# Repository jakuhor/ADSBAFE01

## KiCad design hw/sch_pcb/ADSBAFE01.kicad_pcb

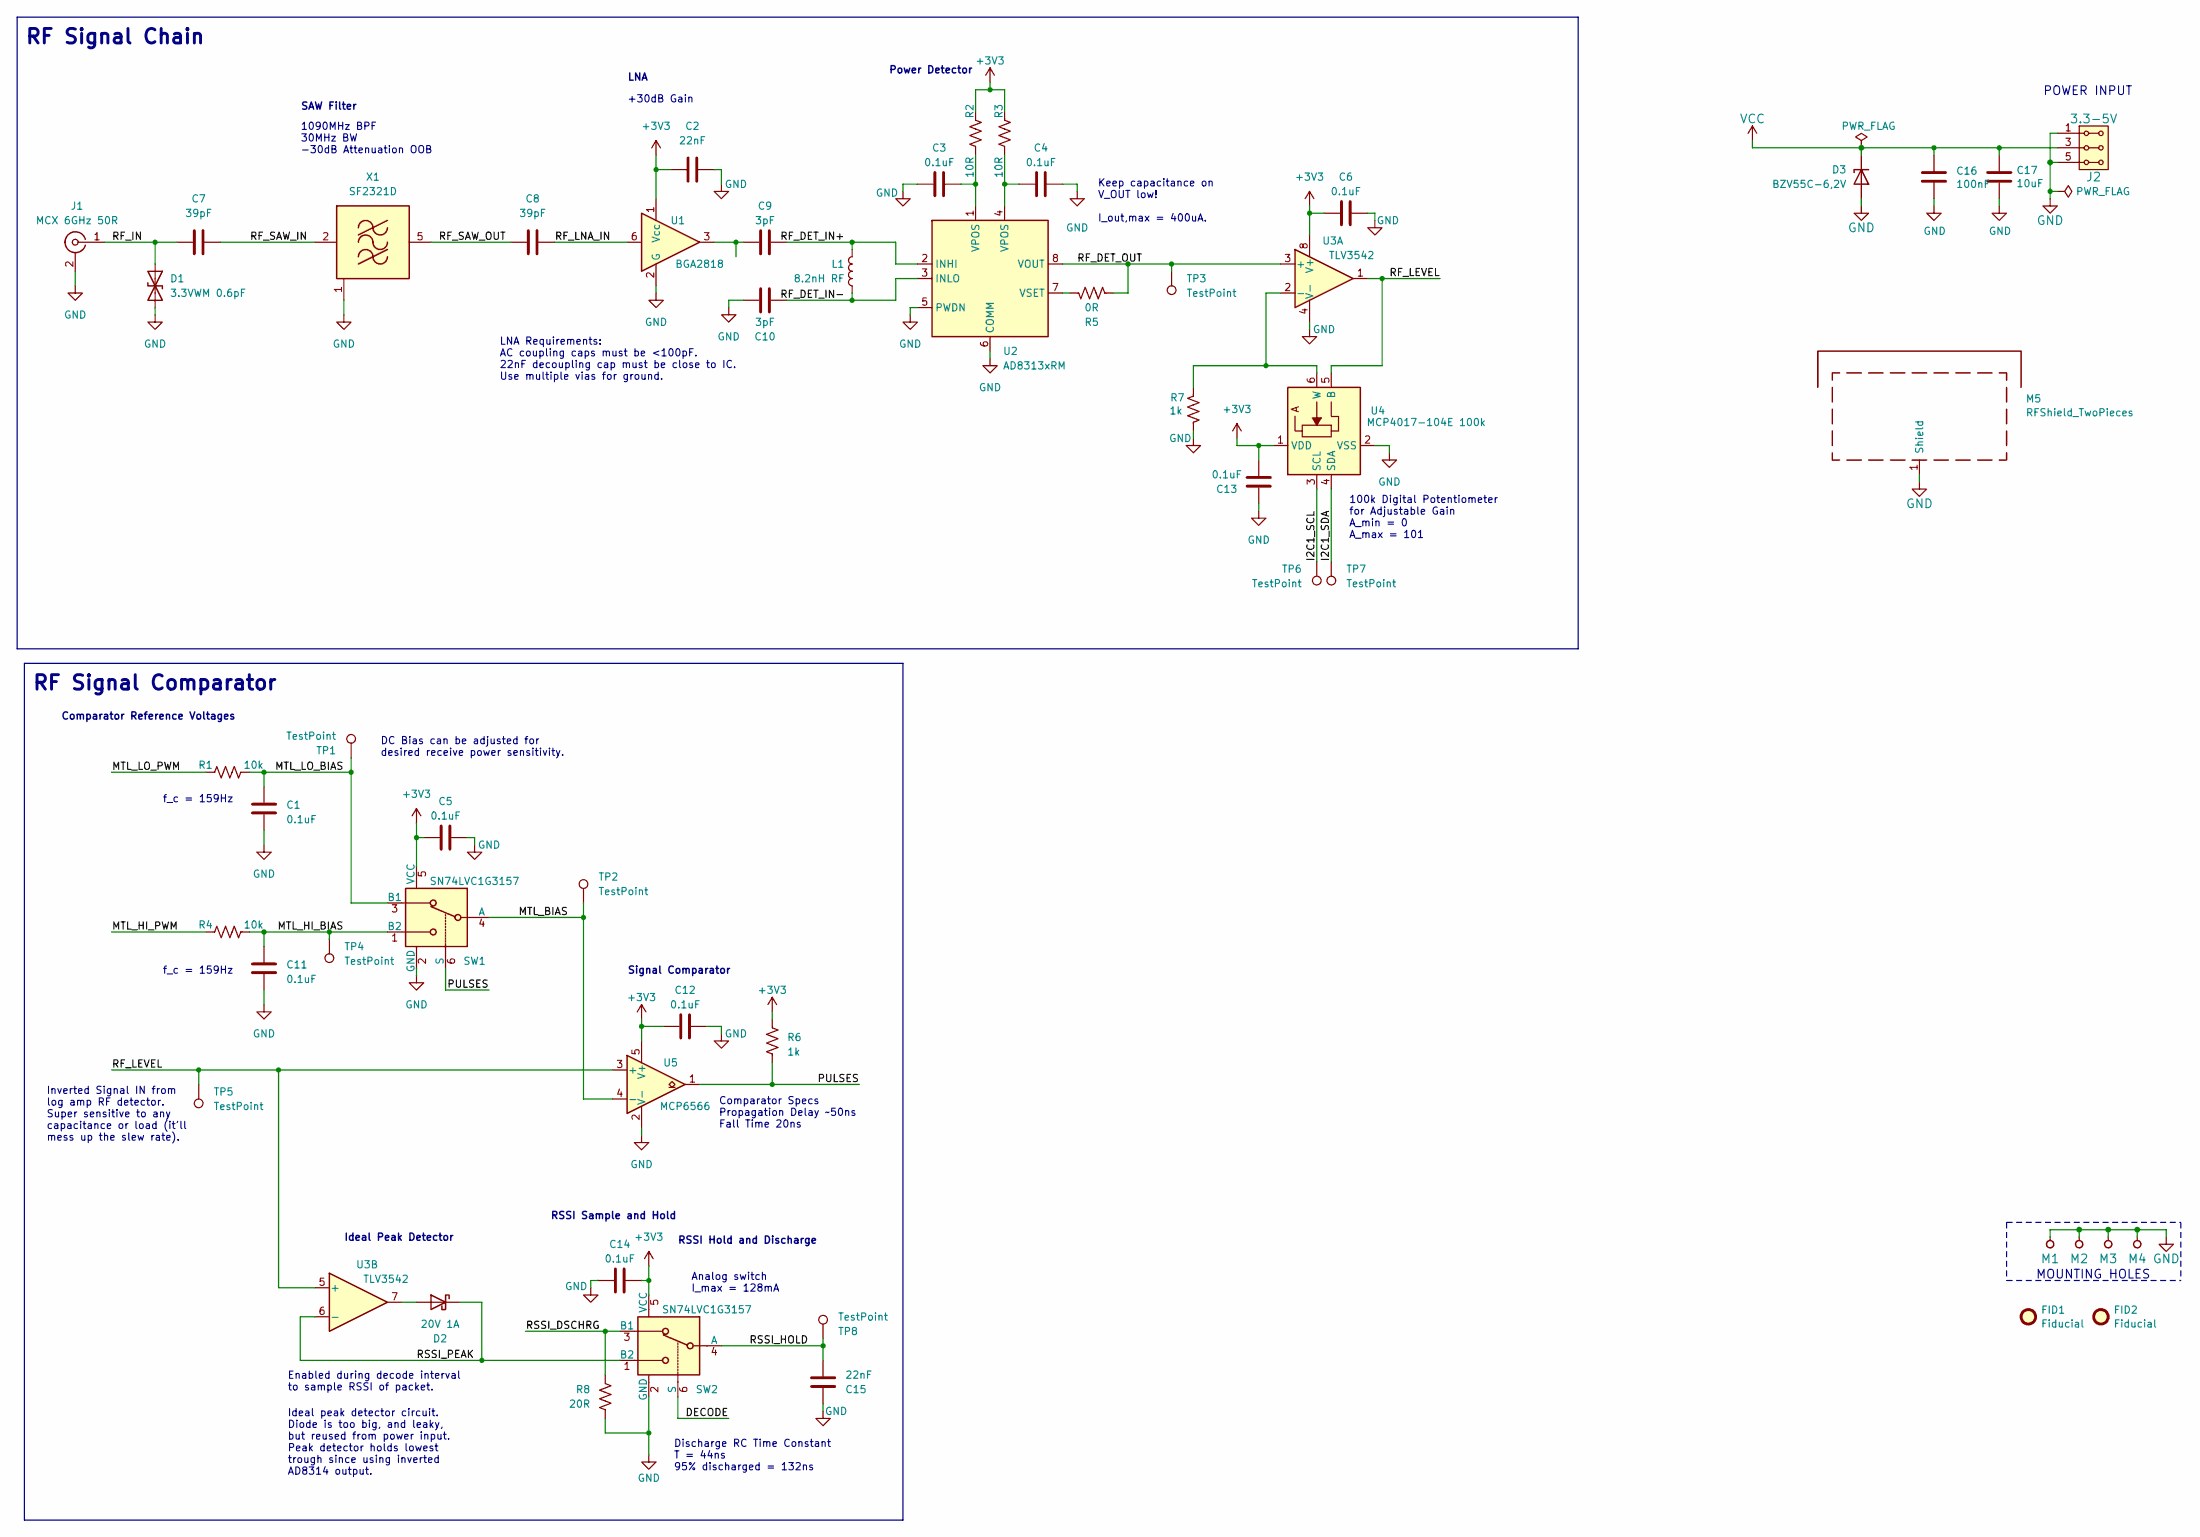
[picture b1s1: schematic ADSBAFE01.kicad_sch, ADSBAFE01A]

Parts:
C1, C3, C4, C5, C6, C11, C12, C13, C14: 0.1uF; C_0402_1005Metric; MPN C60474
C2, C15: 22nF; C_0402_1005Metric; MPN C107026
C7, C8: 39pF; C_0402_1005Metric; MPN C106223
C9, C10: 3pF; C_0402_1005Metric; MPN C1855211
C16: 100nF; C_0805_2012Metric
C17: 10uF; C_0805_2012Metric
D1: 3.3VWM 0.6pF; D_SOD-523; MPN C2912559
D2: 20V 1A; D_SOD-123; MPN C82288
D3: BZV55C-6,2V; D_MiniMELF
FID1, FID2: Fiducial; Fiducial_1mm_Mask2mm
J1: MCX 6GHz 50R; MCX; MPN C88374
J2: 3.3-5V; Straight_2x03
L1: 8.2nH RF; L_0402_1005Metric; MPN C361505
M1, M2, M3, M4: HOLE; MountingHole_3mm
M5: RFShield_TwoPieces; Laird_Technologies_BMI-S-204-F_32.00x32.00mm
R1, R4: 10k; R_0402_1005Metric; MPN C60490
R2, R3: 10R; R_0402_1005Metric; MPN C138066
R5: 0R; R_0402_1005Metric; MPN C60485
R6, R7: 1k; R_0402_1005Metric; MPN C106235
R8: 20R; R_0402_1005Metric; MPN C138031
SW1, SW2: SN74LVC1G3157; SOT-363_SC-70-6; MPN C38663
TP1, TP2, TP3, TP4, TP5, TP6, TP7, TP8: TestPoint; TestPoint_Pad_D1.0mm
U1: BGA2818; SOT-363_SC-70-6; MPN None
U2: AD8313xRM; MSOP-8_3x3mm_P0.65mm; MPN C481897
U3: TLV3542; VSSOP-8_3.0x3.0mm_P0.65mm; MPN C2876465
U4: MCP4017-104E 100k; SOT-363_SC-70-6; MPN C510890
U5: MCP6566; SOT-353_SC-70-5; MPN C623508
X1: SF2321D; Filter_SAW-6_3.8x3.8mm; MPN C3283372

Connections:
+3V3: C2.1, C5.1, C6.1, C12.1, C13.2, C14.2, R2.1, R3.1, R6.1, SW1.5 (VCC), SW2.5 (VCC), U1.1 (Vcc), U3.8 (V+), U4.1 (VDD), U5.5 (V+)
/DECODE: SW2.6 (S)
/I2C1_SCL: TP6.1, U4.3 (SCL)
/I2C1_SDA: TP7.1, U4.4 (SDA)
/MTL_BIAS: SW1.4 (A), TP2.1, U5.4 (-)
/MTL_HI_BIAS: C11.1, R4.1, SW1.1 (B2), TP4.1
/MTL_HI_PWM: R4.2
/MTL_LO_BIAS: C1.1, R1.1, SW1.3 (B1), TP1.1
/MTL_LO_PWM: R1.2
/PULSES: R6.2, SW1.6 (S), U5.1
/RF_DET_IN+: C9.2, L1.1, U2.2 (INHI)
/RF_DET_IN-: C10.2, L1.2, U2.3 (INLO)
/RF_DET_OUT: R5.2, TP3.1, U2.8 (VOUT), U3.3 (+)
/RF_IN: C7.1, D1.1 (A1), J1.1 (In)
/RF_LEVEL: TP5.1, U3.1, U3.5 (+), U4.5 (B), U5.3 (+)
/RF_LNA_IN: C8.2, U1.6
/RF_SAW_IN: C7.2, X1.2 (IN)
/RF_SAW_OUT: C8.1, X1.5 (OUT)
/RSSI_DSCHRG: R8.1, SW2.3 (B1)
/RSSI_HOLD: C15.2, SW2.4 (A), TP8.1
/RSSI_PEAK: D2.1 (K), SW2.1 (B2), U3.6 (-)
GND: C1.2, C2.2, C3.1, C4.2, C5.2, C6.2, C10.1, C11.2, C12.2, C13.1, C14.1, C15.1, C16.2, C17.2, D1.2 (A2), D3.2 (A), J1.2 (Ext), J2.1, J2.2, J2.5, J2.6, M1.1, M2.1, M3.1, M4.1, M5.1 (Shield), R7.2, R8.2, SW1.2 (GND), SW2.2 (GND), U1.2 (G), U1.4 (G), U1.5 (G), U2.5 (PWDN), U2.6 (COMM), U3.4 (V-), U4.2 (VSS), U5.2 (V-), X1.1 (GND), X1.3 (GND), X1.4 (GND), X1.6 (GND)
unnamed: C3.2, R2.2, U2.1 (VPOS)
unnamed: C4.1, R3.2, U2.4 (VPOS)
unnamed: C9.1, U1.3
unnamed: D2.2 (A), U3.7
unnamed: R5.1, U2.7 (VSET)
unnamed: R7.1, U3.2 (-), U4.6 (W)
VCC: C16.1, C17.1, D3.1 (K), J2.3, J2.4

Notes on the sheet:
LNA
Comparator Reference Voltages
1090MHz BPF 30MHz BW -30dB Attenuation OOB
Keep capacitance on V_OUT low! I_out,max = 400uA.
100k Digital Potentiometer for Adjustable Gain A_min = 0 A_max = 101
Ideal Peak Detector
f_c = 159Hz
Analog switch I_max = 128mA
Enabled during decode interval to sample RSSI of packet.
RF Signal Comparator
SAW Filter
MOUNTING HOLES
RF Signal Chain
+30dB Gain
Signal Comparator
f_c = 159Hz
Comparator Specs Propagation Delay ~50ns Fall Time 20ns
RSSI Sample and Hold
DC Bias can be adjusted for desired receive power sensitivity.
LNA Requirements: AC coupling caps must be <100pF. 22nF decoupling cap must be close to IC. Use multiple vias for ground.
RSSI Hold and Discharge
POWER INPUT
Ideal peak detector circuit. Diode is too big, and leaky, but reused from power input. Peak detector holds lowest trough since using inverted AD8314 output.
Power Detector
Discharge RC Time Constant T = 44ns 95% discharged = 132ns
Inverted Signal IN from log amp RF detector. Super sensitive to any capacitance or load (it'll mess up the slew rate).

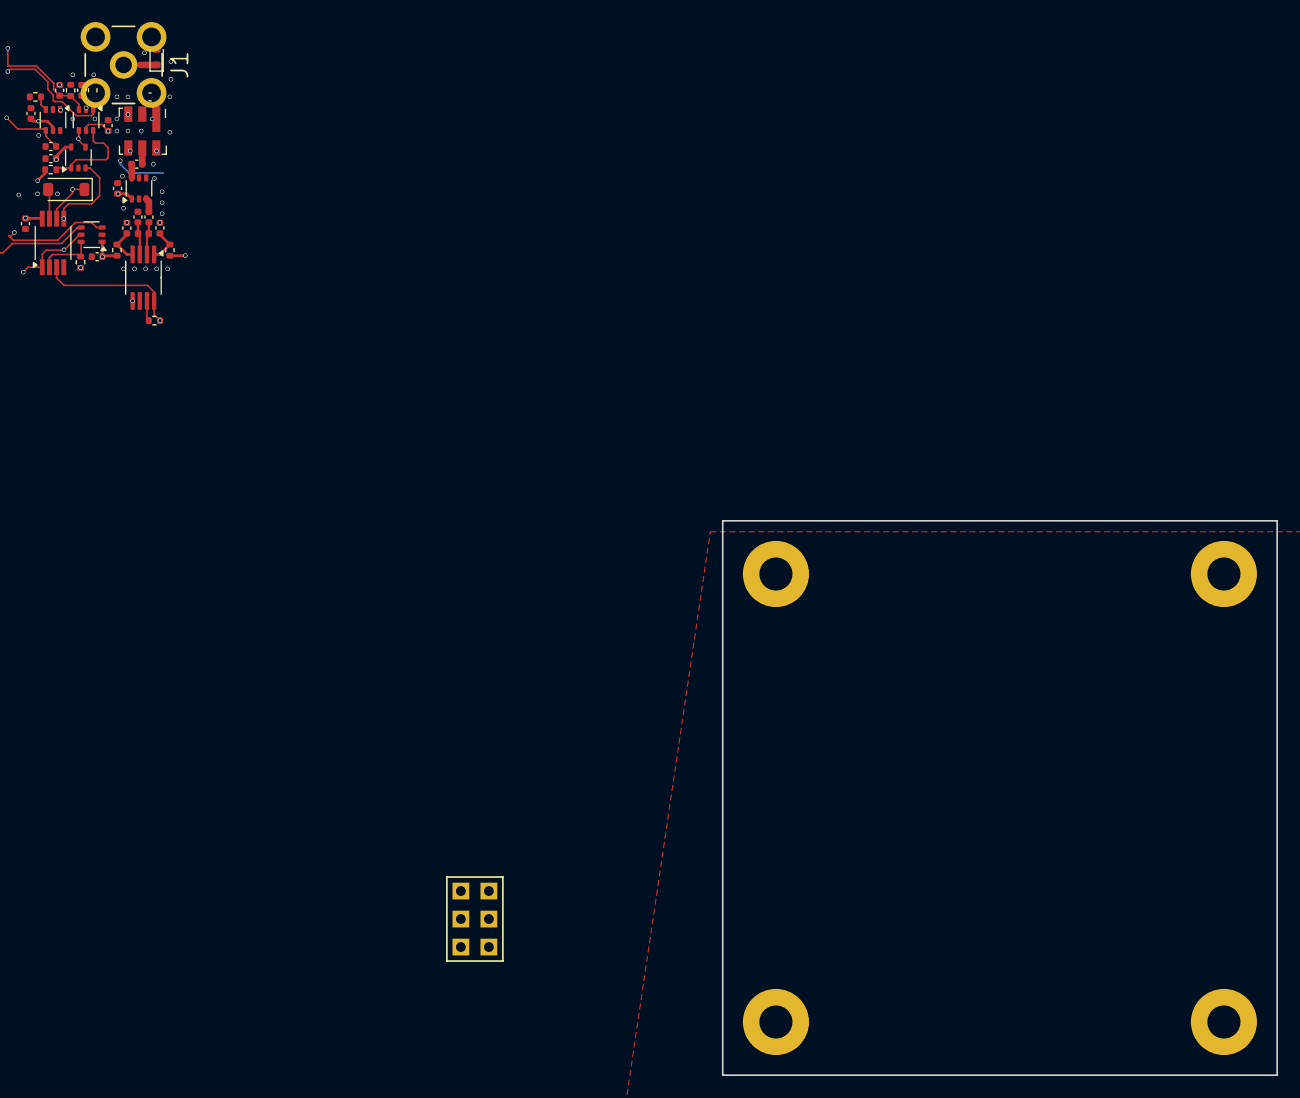
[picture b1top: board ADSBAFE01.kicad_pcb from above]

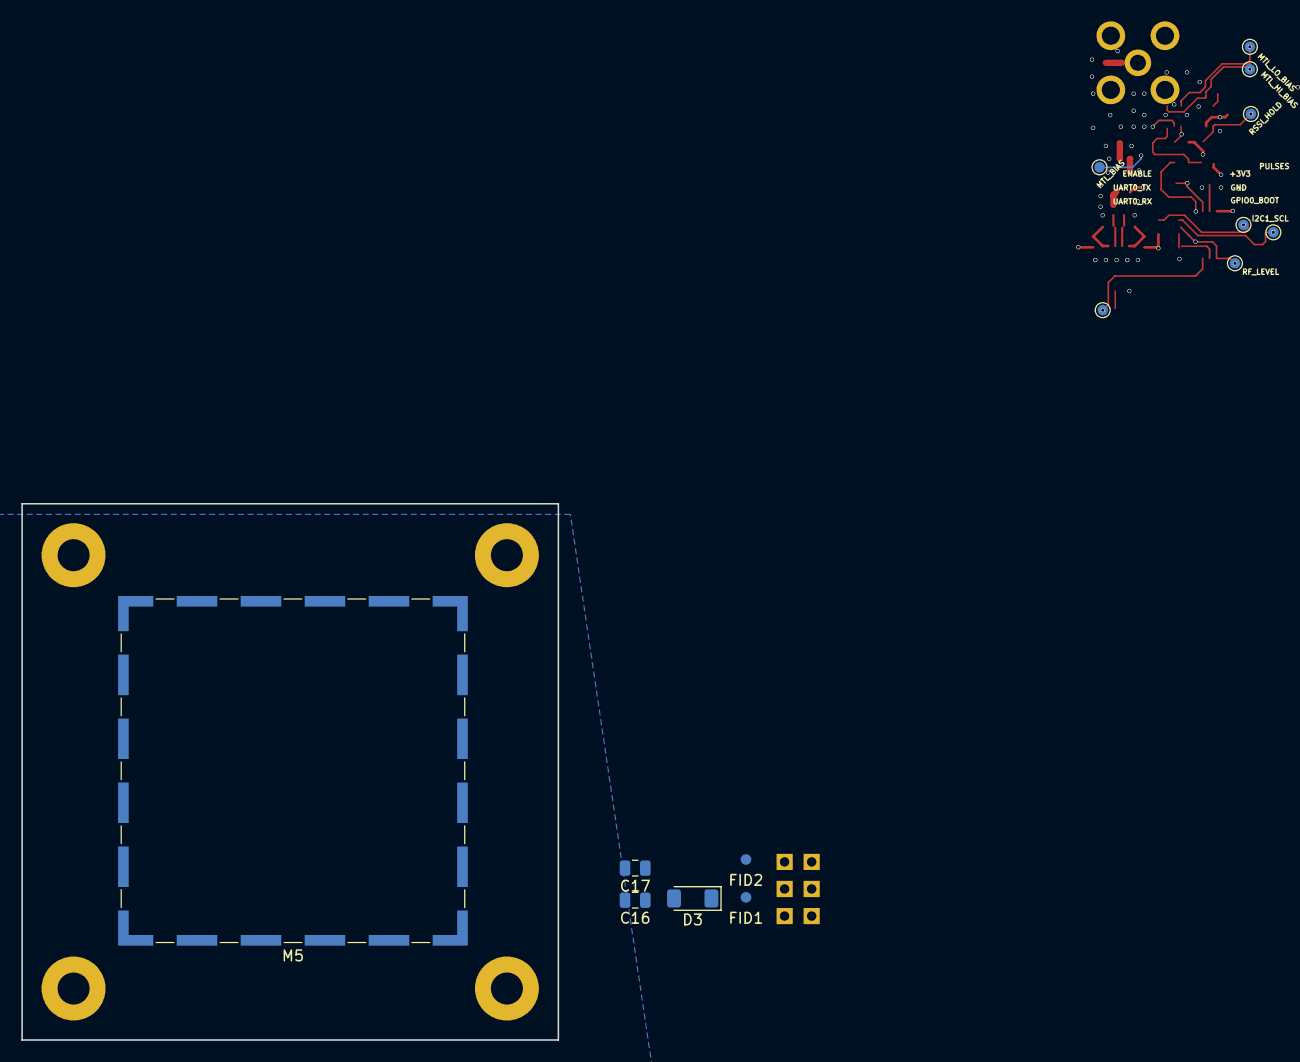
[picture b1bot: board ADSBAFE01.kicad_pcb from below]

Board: 2 copper layers, 50.3 x 50.3 mm, 54 parts (14 on the bottom side), 26 nets.

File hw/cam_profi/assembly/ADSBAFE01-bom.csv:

Component,Description,Part,References,Value,Footprint,Quantity Per PCB,Datasheet,standard cost,oem pn,mpn,ust_id,note
1,Unpolarized capacitor,C,C9C10,3pF,C_0402_1005Metric,2,~,0.01,CQ0402CRNPO9BN3R0,C1855211,,
2,Unpolarized capacitor,C,C7C8,39pF,C_0402_1005Metric,2,~,0.01,CC0402JRNPO9BN390,C106223,,
3,Unpolarized capacitor,C,C2C15,22nF,C_0402_1005Metric,2,~,0.01,CC0402KRX7R9BB223,C107026,,
4,Unpolarized capacitor,C,C1C3C4C5C6C11C12C13C14,0.1uF,C_0402_1005Metric,9,~,0.01,CC0402KRX7R7BB104,C60474,,
5,Unpolarized capacitor,C,C16,100nF,C_0805_2012Metric,1,~,,,,5c70984712875079b91f8b4c,
6,Unpolarized capacitor,C,C17,10uF,C_0805_2012Metric,1,~,,,,5c70984812875079b91f8bbe,
7,Schottky diode,D_Schottky,D2,20V 1A,D_SOD-123,1,~,0.06,"PMEG2010ER,115",C82288,,
8,Bidirectional transient-voltage-suppression diode,D_TVS,D1,3.3VWM 0.6pF,D_SOD-523,1,https://www.onsemi.com/pdf/datasheet/esd7351-d.pdf,0.07,ESD7351XV2T1G,C2912559,,Substituted with TECH PUBLIC dupe due to no stock of onsemi part.
9,Zener diode,D_Zener,D3,"BZV55C-6,2V",D_MiniMELF,1,~,,,,604b0326128750769e5b0f93,
10,"2x03 2.54 mm pitch header, 2 pins next to each other are connected",HEADER_2x03_PARALLEL,J2,3.3-5V,Straight_2x03,1,,,,,,
11,"coaxial connector (BNC, SMA, SMB, SMC, Cinch/RCA, LEMO, ...)",Conn_Coaxial,J1,MCX 6GHz 50R,MCX,1,~,0.41,U.FL-R-SMT-1(80),C88374,,"(80) suffix denotes reel size, can be substituted."
12,Inductor,L,L1,8.2nH RF,L_0402_1005Metric,1,~,0.03,SDWL1005C8N2JSTF,C361505,,Looking for a wire wound inductor with similar performance to Coilcraft 0402HP-8N2.
13,Two-piece EMI RF shielding cabinet,RFShield_TwoPieces,M5,RFShield_TwoPieces,Laird_Technologies_BMI-S-204-F_32.00x32.00mm,1,~,,,,5c72751c1287500b4e11301a,
14,"Resistor, US symbol",R_US,R5,0R,R_0402_1005Metric,1,~,0.01,RC0402JR-070RL,C60485,,
15,"Resistor, US symbol",R_US,R2R3,10R,R_0402_1005Metric,2,~,0.01,RC0402FR-0710RL,C138066,,
16,"Resistor, US symbol",R_US,R8,20R,R_0402_1005Metric,1,~,0.01,RC0402FR-0720RL,C138031,,
17,"Resistor, US symbol",R_US,R6R7,1k,R_0402_1005Metric,2,~,0.01,RC0402FR-071KL,C106235,,
18,"Resistor, US symbol",R_US,R1R4,10k,R_0402_1005Metric,2,~,0.01,RC0402FR-0710KL,C60490,,
19,SPDT Analog Switch 1.65V-5.5V 0.5ns 6R,SN74LVC1G3157,SW1SW2,SN74LVC1G3157,SOT-363_SC-70-6,2,https://www.ti.com/lit/ds/symlink/sn74lvc1g3157.pdf,0.07,SN74LVC1G3157DCKR,C38663,,
20,"100 MHz to 2.5 GHz, 80 dB Logarithmic Detector / Controller, MSOP-8",AD8313xRM,U2,AD8313xRM,MSOP-8_3x3mm_P0.65mm,1,https://www.analog.com/media/en/technical-documentation/data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,3.35,AD8313ARMZ,C481897,,
21,"MMIC wideband amplifier, DC-2.2GHz, +30dB @ 2150MHz, 3.3V, SOT-363",BGA2818,U1,BGA2818,SOT-363_SC-70-6,1,https://www.nxp.com/docs/en/data-sheet/BGA2818.pdf,0.14,"BGA2818,115",None,,Not available from LCSC.
22,"Low-Cost 128-Step Volatile I2C Digital Potentiometer, SC-70-6",MCP4017-xxxxLT,U4,MCP4017-104E 100k,SOT-363_SC-70-6,1,http://ww1.microchip.com/downloads/en/DeviceDoc/22147a.pdf,0.54,MCP4017T-104E/LT,C510890,,
23,"Single 1.8V Low-Power Open-Drain Output Comparator, SOT-23-5/SC-70",MCP6566,U5,MCP6566,SOT-353_SC-70-5,1,http://ww1.microchip.com/downloads/en/DeviceDoc/MCP6566-6R-6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,0.48,MCP6566T-E/LT,C623508,,Out of stock at LCSC.
24,"200-MHz, Rail-to-Rail I/O, VSSOP-8",TLV3542,U3,TLV3542,VSSOP-8_3.0x3.0mm_P0.65mm,1,https://www.ti.com/lit/ds/symlink/tlv3542.pdf,0.84,TLV3542IDGKR,C2876465,,
25,"Bandpass Filter, SAW filter 6-pin",SAW-6 Filter,X1,SF2321D,Filter_SAW-6_3.8x3.8mm,1,https://www.mouser.com/datasheet/2/1100/sf2321d-1917641.pdf,1.10,SF2321D,C3283372,,Out of stock at LCSC.

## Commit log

2026-01-19 Update workflow files
2026-01-19 Update metadata files
2026-01-19 Add initial KiCAD design files.
2026-01-19 Update actions products
2026-02-08 schematic first iteration
